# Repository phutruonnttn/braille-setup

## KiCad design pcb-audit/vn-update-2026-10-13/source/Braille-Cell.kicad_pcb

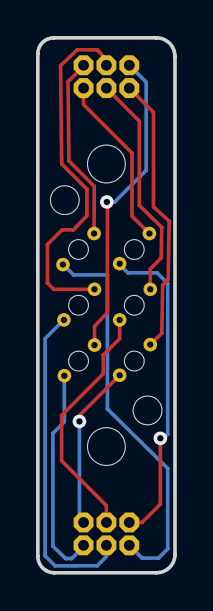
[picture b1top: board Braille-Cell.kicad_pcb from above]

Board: 2 copper layers, 7.6 x 29.7 mm, 12 parts (0 on the bottom side), 12 nets.

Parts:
COIL_TERMINALS: 6 coils / 12 exposed PTH solder terminals
U$1: BRAILLE-6
UNK_HOLE_0: dummyfp0
UNK_HOLE_1: dummyfp1
UNK_HOLE_2: dummyfp2
UNK_HOLE_3: dummyfp3
UNK_HOLE_4: dummyfp4
UNK_HOLE_5: dummyfp5
UNK_HOLE_6: dummyfp6
UNK_HOLE_7: dummyfp7
UNK_HOLE_8: dummyfp8
UNK_HOLE_9: dummyfp9

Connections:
1A: COIL_TERMINALS.1A, U$1.P$1
1B: COIL_TERMINALS.1B, U$1.P$2
2A: COIL_TERMINALS.2A, U$1.P$3
2B: COIL_TERMINALS.2B, U$1.P$4
3A: COIL_TERMINALS.3A, U$1.P$5
3B: COIL_TERMINALS.3B, U$1.P$6
4A: COIL_TERMINALS.4A, U$1.P$7
4B: COIL_TERMINALS.4B, U$1.P$8
5A: COIL_TERMINALS.5A, U$1.P$9
5B: COIL_TERMINALS.5B, U$1.P$10
6A: COIL_TERMINALS.6A, U$1.P$11
6B: COIL_TERMINALS.6B, U$1.P$12

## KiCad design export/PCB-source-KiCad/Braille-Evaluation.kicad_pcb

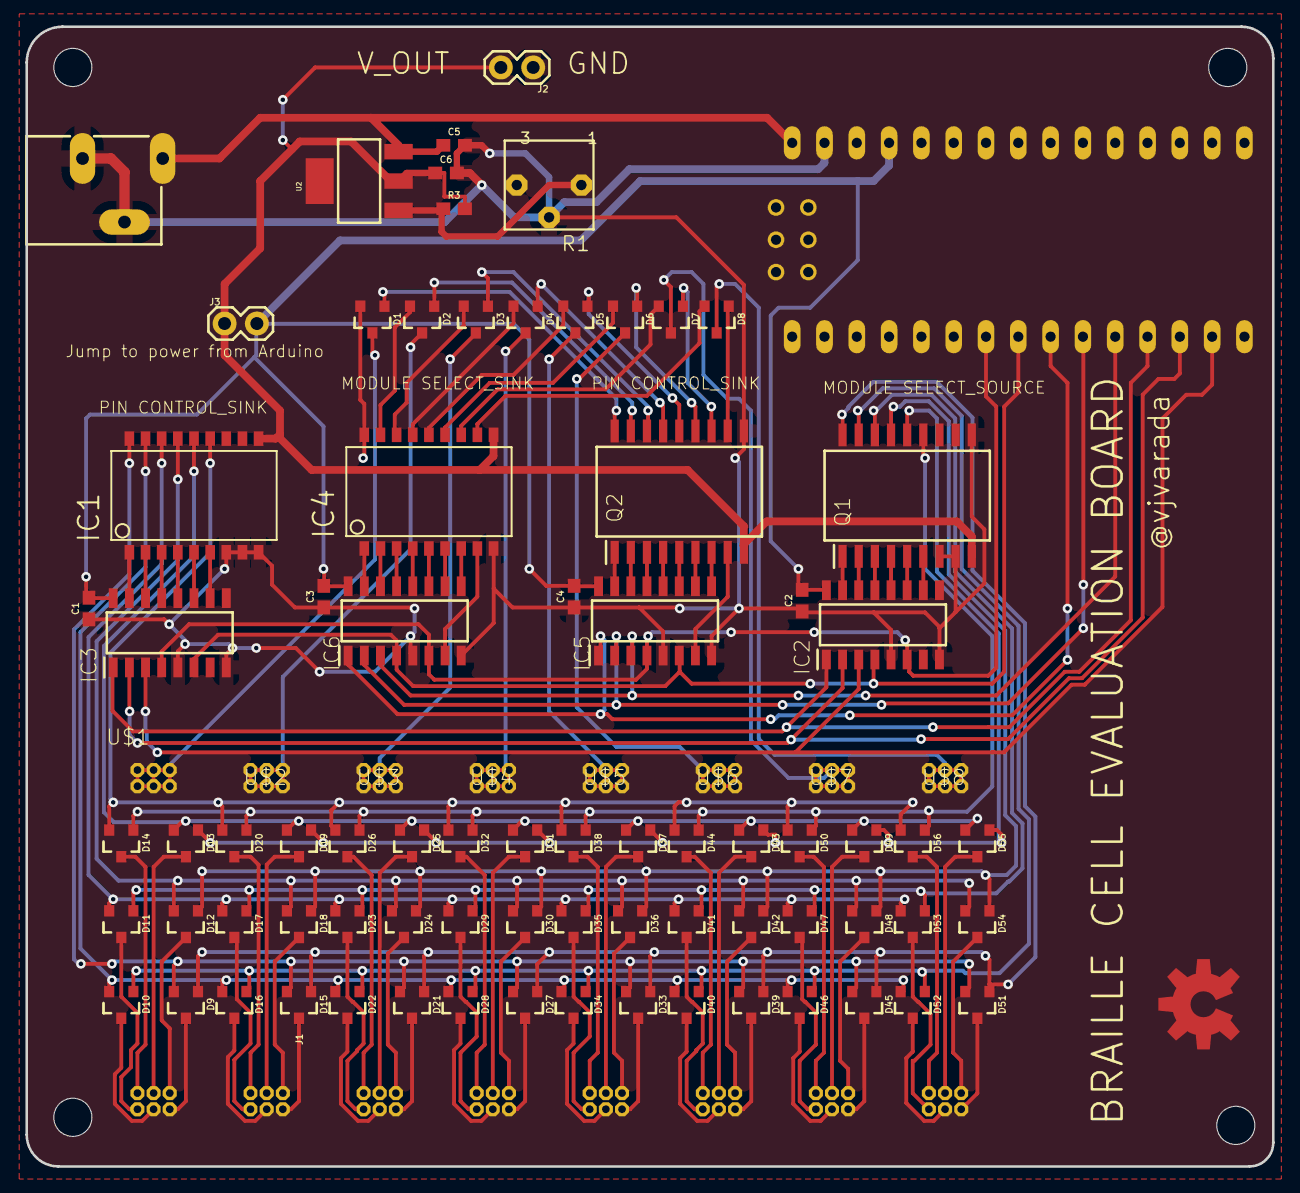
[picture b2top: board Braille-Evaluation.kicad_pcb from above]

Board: 2 copper layers, 98.0 x 89.6 mm, 90 parts (0 on the bottom side), 125 nets.

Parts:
C1, C2, C3, C4, C5: 0.1uF; 0603
C6: 1uf; 0603
D1, D2, D3, D4, D5, D6, D7, D8, D9, D10, D11, D12, D13, D14, D15, D16, D17, D18, D19, D20, D21, D22, D23, D24, D25, D26, D27, D28, D29, D30, D31, D32, D33, D34, D35, D36, D37, D38, D39, D40, D41, D42, D43, D44, D45, D46, D47, D48, D49, D50, D51, D52, D53, D54, D55, D56: 200mA/70V; SOT23-3
IC1, IC4: TBD62083AFG; SO18
IC2, IC3, IC5, IC6: 74HC238D; SOIC127P600X175-16N
J1: POWER_JACKSLT; POWER_JACK_SLOT
J2, J3: 1X02
LOGO1: OSHW-LOGOL-COPPER; OSHW-LOGO-L_COPPER
Q1, Q2: TBD62783AFG,EL; SOIC127P1030X245-18N
R1: 1k; 3362P
R3: 240R; 0603
U2: LM317; SOT223
U$1, U$2, U$3, U$4, U$5, U$6, U$7, U$8: BRAILLE-6
U$9: NANO
UNK_HOLE_0: dummyfp0
UNK_HOLE_1: dummyfp1
UNK_HOLE_2: dummyfp2
UNK_HOLE_3: dummyfp3

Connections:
GND: C1.1, C2.1, C3.1, C4.1, C5.2, C6.2, IC1.7, IC1.8, IC1.9, IC2.5, IC2.8, IC3.5, IC3.8, IC4.9, IC5.5, IC5.8, IC6.5, IC6.8, J1.GND@1, J1.GND@2, J2.1, Q1.7, Q1.8, Q1.10, Q2.10, R1.2, U$9.GND
MOD_0: IC5.1, IC6.1, U$9.D6
MOD_1: IC5.2, IC6.2, U$9.D7
MOD_2: IC5.3, IC6.3, U$9.D8
unnamed: IC2.15, Q1.1
unnamed: IC2.14, Q1.2
unnamed: IC2.13, Q1.3
unnamed: IC2.12, Q1.4
unnamed: IC2.11, Q1.5
unnamed: IC2.10, Q1.6
unnamed: IC1.1, IC3.15
unnamed: IC1.2, IC3.14
unnamed: IC1.3, IC3.13
unnamed: IC1.4, IC3.12
unnamed: IC1.5, IC3.11
unnamed: IC5.15, Q2.1
unnamed: IC5.14, Q2.2
unnamed: IC5.13, Q2.3
unnamed: IC5.12, Q2.4
unnamed: IC5.11, Q2.5
unnamed: D1.1, Q2.18
unnamed: IC4.1, IC6.15
unnamed: IC4.2, IC6.14
unnamed: IC4.3, IC6.13
unnamed: IC4.4, IC6.12
unnamed: IC4.5, IC6.11
unnamed: D2.1, Q2.17
unnamed: IC5.10, Q2.6
unnamed: D3.1, Q2.16
unnamed: IC5.9, Q2.7
unnamed: IC5.7, Q2.8
unnamed: IC4.8, IC6.7
unnamed: IC4.6, IC6.10
unnamed: IC4.7, IC6.9
unnamed: D4.1, Q2.15
unnamed: IC1.6, IC3.10
unnamed: D5.1, Q2.14
unnamed: D6.1, Q2.13
unnamed: D7.1, Q2.12
unnamed: D8.1, Q2.11
unnamed: D1.2, IC4.18
unnamed: D9.3, U$1.P$2
unnamed: D2.2, IC4.17
unnamed: D3.3, U$3.P$1, U$3.P$3, U$3.P$5, U$3.P$7, U$3.P$9, U$3.P$11
unnamed: D4.3, U$4.P$1, U$4.P$3, U$4.P$5, U$4.P$7, U$4.P$9, U$4.P$11
unnamed: D5.3, U$5.P$1, U$5.P$3, U$5.P$5, U$5.P$7, U$5.P$9, U$5.P$11
unnamed: D6.3, U$6.P$1, U$6.P$3, U$6.P$5, U$6.P$7, U$6.P$9, U$6.P$11
unnamed: D7.3, U$7.P$1, U$7.P$3, U$7.P$5, U$7.P$7, U$7.P$9, U$7.P$11
unnamed: D8.3, U$8.P$1, U$8.P$3, U$8.P$5, U$8.P$7, U$8.P$9, U$8.P$11
unnamed: D10.3, U$1.P$4
unnamed: D11.3, U$1.P$6
unnamed: D12.3, U$1.P$8
unnamed: D13.3, U$1.P$10
unnamed: D14.3, U$1.P$12
unnamed: D21.3, U$3.P$2
unnamed: D10.1, D16.1, D22.1, D28.1, D34.1, D40.1, D46.1, D52.1, Q1.17
unnamed: D11.1, D17.1, D23.1, D29.1, D35.1, D41.1, D47.1, D53.1, Q1.16
unnamed: D12.1, D18.1, D24.1, D30.1, D36.1, D42.1, D48.1, D54.1, Q1.15
unnamed: D27.3, U$4.P$2
unnamed: D33.3, U$5.P$2
unnamed: D9.2, D15.2, D21.2, D27.2, D33.2, D39.2, D45.2, D51.2, IC1.18
unnamed: D39.3, U$6.P$2
unnamed: D11.2, D17.2, D23.2, D29.2, D35.2, D41.2, D47.2, D53.2, IC1.16
unnamed: D12.2, D18.2, D24.2, D30.2, D36.2, D42.2, D48.2, D54.2, IC1.15
unnamed: D13.2, D19.2, D25.2, D31.2, D37.2, D43.2, D49.2, D55.2, IC1.14
unnamed: D14.2, D20.2, D26.2, D32.2, D38.2, D44.2, D50.2, D56.2, IC1.13
unnamed: D15.3, U$2.P$2
unnamed: D16.3, U$2.P$4
unnamed: D17.3, U$2.P$6
unnamed: D18.3, U$2.P$8
unnamed: D19.3, U$2.P$10
unnamed: D20.3, U$2.P$12
unnamed: D28.3, U$4.P$4
unnamed: D22.3, U$3.P$4
unnamed: D23.3, U$3.P$6
unnamed: D24.3, U$3.P$8
unnamed: D25.3, U$3.P$10
unnamed: D26.3, U$3.P$12
unnamed: D45.3, U$7.P$2
unnamed: D10.2, D16.2, D22.2, D28.2, D34.2, D40.2, D46.2, D52.2, IC1.17
unnamed: D51.3, U$8.P$2
unnamed: D1.3, U$1.P$1, U$1.P$3, U$1.P$5, U$1.P$7, U$1.P$9, U$1.P$11
unnamed: D2.3, U$2.P$1, U$2.P$3, U$2.P$5, U$2.P$7, U$2.P$9, U$2.P$11
unnamed: D29.3, U$4.P$6
unnamed: D30.3, U$4.P$8
unnamed: D3.2, IC4.16
unnamed: D13.1, D19.1, D25.1, D31.1, D37.1, D43.1, D49.1, D55.1, Q1.14
unnamed: D14.1, D20.1, D26.1, D32.1, D38.1, D44.1, D50.1, D56.1, Q1.13
unnamed: D4.2, IC4.15
unnamed: D5.2, IC4.14
unnamed: D6.2, IC4.13
unnamed: D7.2, IC4.12
unnamed: D8.2, IC4.11
unnamed: D31.3, U$4.P$10
unnamed: D32.3, U$4.P$12
unnamed: R1.1, R3.1, U2.1
unnamed: D34.3, U$5.P$4
unnamed: D35.3, U$5.P$6
unnamed: D36.3, U$5.P$8
unnamed: D37.3, U$5.P$10
unnamed: D38.3, U$5.P$12
unnamed: D40.3, U$6.P$4
unnamed: D41.3, U$6.P$6
unnamed: D42.3, U$6.P$8
unnamed: D43.3, U$6.P$10
unnamed: D44.3, U$6.P$12
unnamed: D46.3, U$7.P$4
unnamed: D47.3, U$7.P$6
unnamed: D48.3, U$7.P$8
unnamed: D49.3, U$7.P$10
unnamed: D50.3, U$7.P$12
unnamed: D52.3, U$8.P$4
unnamed: D53.3, U$8.P$6
unnamed: D54.3, U$8.P$8
unnamed: D55.3, U$8.P$10
unnamed: D56.3, U$8.P$12
unnamed: D9.1, D15.1, D21.1, D27.1, D33.1, D39.1, D45.1, D51.1, Q1.18
PIN_0: IC2.1, IC3.1, U$9.D9
PIN_1: IC2.2, IC3.2, U$9.D10
PIN_2: IC2.3, IC3.3, U$9.D11
RAW: C5.1, J1.PWR, U2.3, U$9.RAW
RESET: IC2.6, IC3.4, IC5.4, IC6.6, U$9.D4
SET: IC2.4, IC3.6, IC5.6, IC6.4, U$9.D5
VCC: C1.2, C2.2, C3.2, C4.2, IC2.16, IC3.16, IC5.16, IC6.16, J3.2, U$9.5V
V_DRIVE: C6.1, IC1.10, IC4.10, J2.2, J3.1, Q1.9, Q2.9, R3.2, U2.2
